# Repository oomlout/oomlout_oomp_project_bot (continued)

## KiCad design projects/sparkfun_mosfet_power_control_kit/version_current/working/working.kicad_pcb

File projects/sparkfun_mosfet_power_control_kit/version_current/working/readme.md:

# OOMP Project  
## MOSFET_Power_Control_Kit  by sparkfun  
  
oomp key: oomp_projects_flat_sparkfun_mosfet_power_control_kit  
(snippet of original readme)  
  
SparkFun MOSFET Power Control Kit  
===================================  

[*SparkFun MOSFET Power Control Kit (COM-12959)*](https://www.sparkfun.com/products/12959)  
  
This is the SparkFun MOSFET Power Control Kit, a breakout PTH soldering kit for for the RFP30N06LE N-Channel MOSFET.  
What we really like about this particular MOSFET is that it’s very common and offers very low on-resistance with a control   
(gate) voltage that is compatible with any 3-5V microcontroller or mechanical switch. This allows you to control high-power  
 devices with very low-power control mechanisms.  
   
 Repository Contents  
-------------------  
* **/Hardware** - All Eagle design files (.brd, .sch)  
  
Product Versions  
----------------  
* [COM-10256](https://www.sparkfun.com/products/retired/10256)- Version 1.0. Retired.   
  
License Information  
-------------------  
The hardware is released under [Creative Commons ShareAlike 4.0 International](https://creativecommons.org/licenses/by-sa/4.0/).  
  
Distributed as-is; no warranty is given.  
  
  full source readme at [readme_src.md](readme_src.md)  
  
source repo at: [https://github.com/sparkfun/MOSFET_Power_Control_Kit](https://github.com/sparkfun/MOSFET_Power_Control_Kit)  
## Board  

## Schematic  

[schematic pdf](working_schematic.pdf)  
## Images

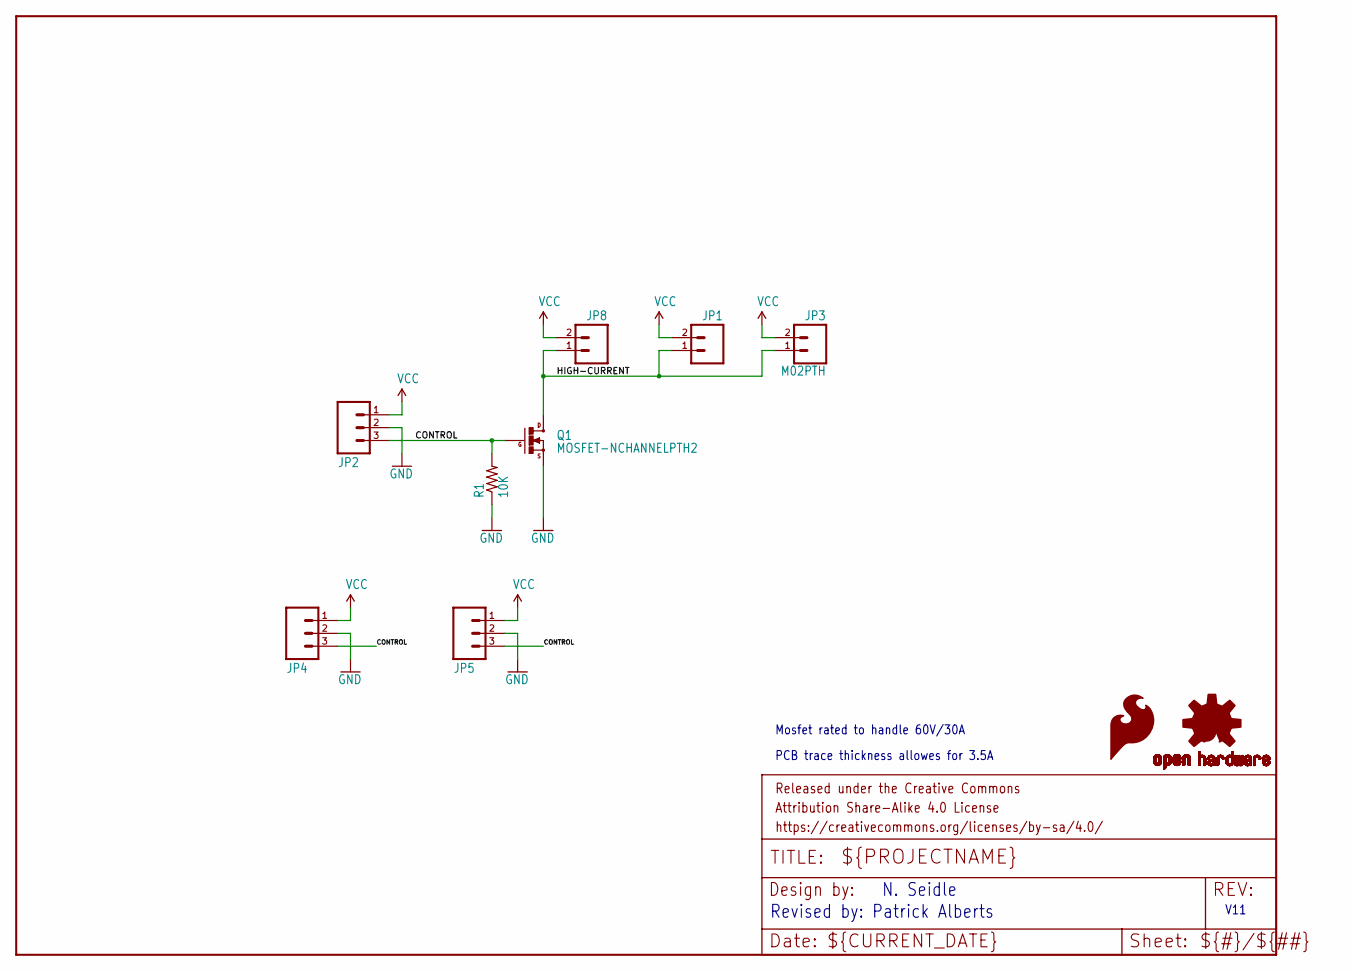
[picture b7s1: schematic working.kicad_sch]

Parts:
FRAME1: FRAME-LETTER; CREATIVE_COMMONS
JP1: M023.5MM; SCREWTERMINAL-3.5MM-2
JP2: M03JST-PTH; JST-3-PTH
JP3: M02PTH; 1X02
JP4: M03SCREW; SCREWTERMINAL-3.5MM-3
JP5: M03PTH; 1X03
JP8: M02JST-PTH-2; JST-2-PTH
LOGO1: OSHW-LOGOS; OSHW-LOGO-S
LOGO2: SFE_LOGO_FLAME.1_INCH; SFE_LOGO_FLAME_.1
Q1: MOSFET-NCHANNELPTH2; TO220V
R1: 10K; AXIAL-0.3

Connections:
CONTROL: JP2.3, JP4.3, JP5.3, Q1.1 (G), R1.P$2 (2)
GND: JP2.2, JP4.2, JP5.2, Q1.3 (S), R1.P$1 (1)
HIGH-CURRENT: JP1.1, JP3.1, JP8.1, Q1.2 (D)
VCC: JP1.2, JP2.1, JP3.2, JP4.1, JP5.1, JP8.2

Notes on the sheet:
Revised by: Patrick Alberts
PCB trace thickness allowes for 3.5A
N. Seidle
V11
Mosfet rated to handle 60V/30A

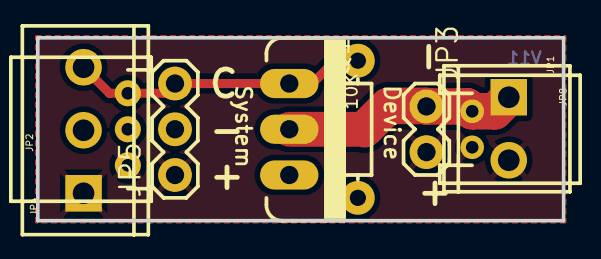
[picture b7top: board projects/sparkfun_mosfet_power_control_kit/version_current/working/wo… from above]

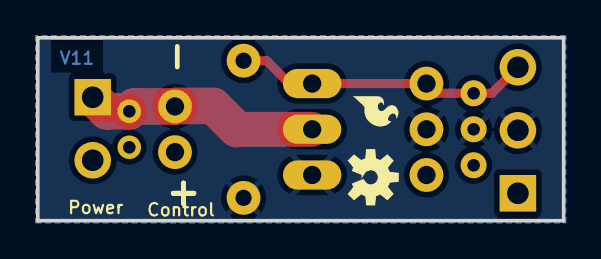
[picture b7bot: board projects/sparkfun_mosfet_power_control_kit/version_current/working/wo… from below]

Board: 2 copper layers, 29.2 x 10.2 mm, 11 parts (2 on the bottom side), 4 nets.

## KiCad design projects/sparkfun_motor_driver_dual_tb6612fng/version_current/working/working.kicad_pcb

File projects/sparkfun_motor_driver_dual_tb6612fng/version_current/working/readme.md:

# Motor_Driver-Dual_TB6612FNG by sparkfun  
This is a harvested standardized copy of a project from github.  
The original project can be found at:  
https://github.com/sparkfun/Motor_Driver-Dual_TB6612FNG  
Please consult that link for additional, details, files, and license information.  
Note: It was auto harvested and if the original repo had more than one board file or anything out of the ordinary the files here are likely not representative.

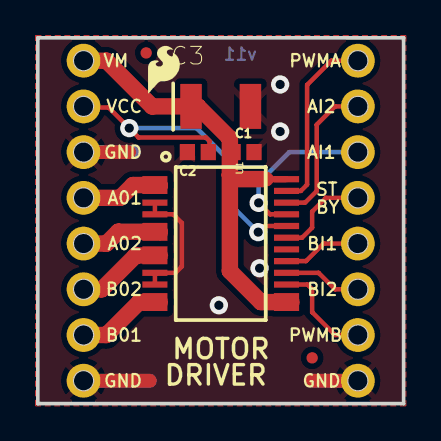
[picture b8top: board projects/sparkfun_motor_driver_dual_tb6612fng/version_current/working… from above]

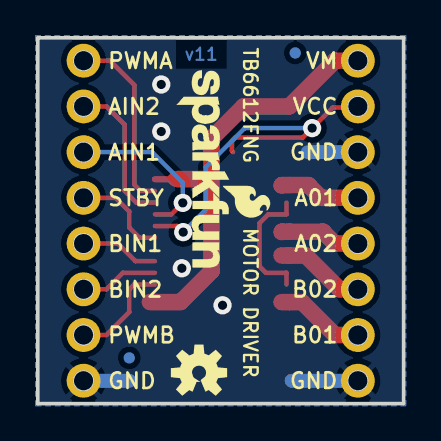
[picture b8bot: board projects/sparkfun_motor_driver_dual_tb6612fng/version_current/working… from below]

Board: 16 copper layers, 20.3 x 20.3 mm, 14 parts (4 on the bottom side), 14 nets.

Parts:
C1, C2: 0.1uF; 0402
C3: 10uF; EIA3528
FD1, FD2, FD3, FD4: FIDUCIALUFIDUCIAL; FIDUCIAL-MICRO
FRAME1: FRAME-LETTER; CREATIVE_COMMONS
JP1, JP2: 1X08_OFFSET_REDUCED
LOGO1: SFE_LOGO_FLAME.1_INCH; SFE_LOGO_FLAME_.1
LOGO2: OSHW-LOGOS; OSHW-LOGO-S
LOGO4: SFE_LOGO_NAME_FLAME.1_INCH; SFE_LOGO_NAME_FLAME_.1
U1: TB6612FNG; SSOP24

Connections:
A01: JP1.5, U1.1, U1.2
A02: JP1.4, U1.5, U1.6
AIN1: JP2.3, U1.21
AIN2: JP2.2, U1.22
B01: JP1.2, U1.11, U1.12
B02: JP1.3, U1.7, U1.8
BIN1: JP2.5, U1.17
BIN2: JP2.6, U1.16
GND: C1.2, C2.2, C3.C, JP1.1, JP1.6, JP2.8, U1.3, U1.4, U1.9, U1.10, U1.18
PWMA: JP2.1, U1.23
PWMB: JP2.7, U1.15
STBY: JP2.4, U1.19
VCC: C2.1, JP1.7, U1.20
VM: C1.1, C3.A, JP1.8, U1.13, U1.14, U1.24
